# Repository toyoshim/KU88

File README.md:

# KU88
PCB and firmware to convert USB's MD mini controller to PC-8801 keyboard.

# Usage
START button changes the input mode as Normal Mode -> Tenkey Mode -> Normal Mode ...

## Normal Mode
Suitable keymap for RPG games such as The Legend of Heroes, and Hydlide.
Keyname written inside `()` is used while SELECT is pressed.
```
 7(7) 8(8) 9(9)
 4(4)  +   6(6)    F1(W) F2(R) F3(C)
 1(1) 2(2) 3(3)     RET   SPC  Z(ESC)
```
The numbers are 10-Key variants without the START being pressed, and normal one
with the START being pressed.
 
## Tenkey Mode
Suitable keymap for ADV games such as JESUS.
```
      S(V)       
 Y(Z)  +   N(C)     1(7)  2(8)  3(9)
     SPC(X)         0(4)  ,(5)  .(6)
```

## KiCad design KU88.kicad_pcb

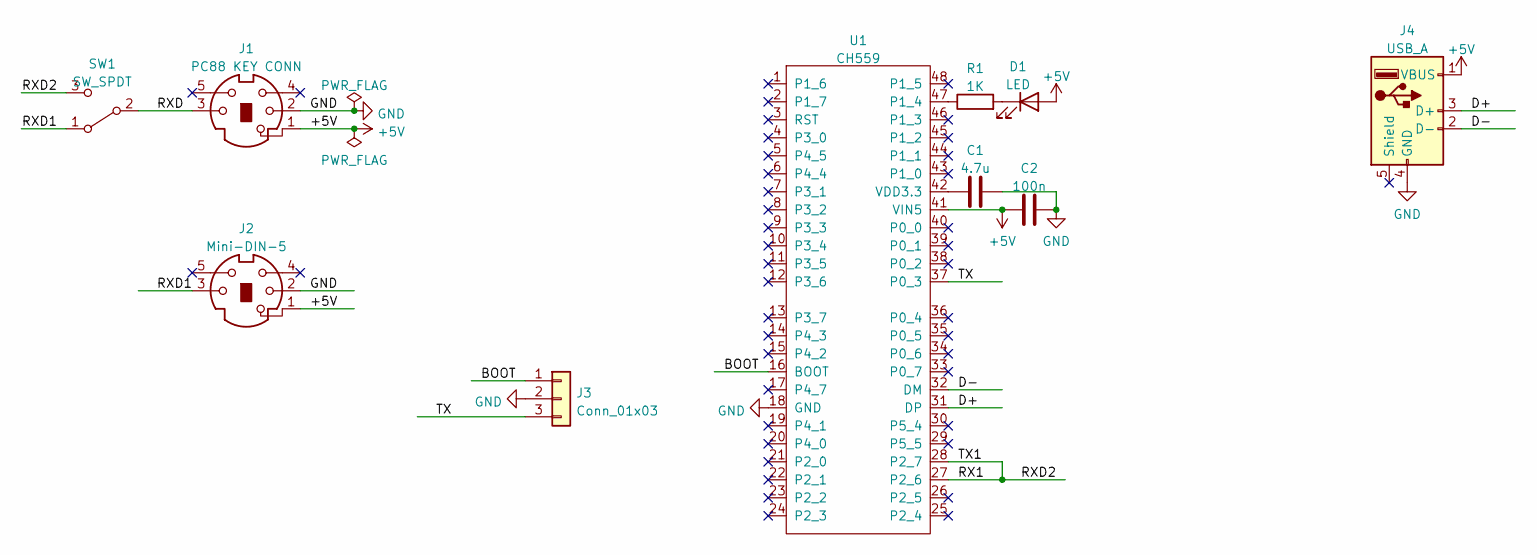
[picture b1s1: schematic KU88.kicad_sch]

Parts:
C1: 4.7u; C_0603_1608Metric_Pad1.08x0.95mm_HandSolder
C2: 100n; C_0603_1608Metric_Pad1.08x0.95mm_HandSolder
D1: LED; D_0603_1608Metric_Pad1.05x0.95mm_HandSolder
J1: PC88 KEY CONN; Mini-DIN 5 Pin Connector
J2: Mini-DIN-5; Mini-DIN 5 Pin Connector
J3: Conn_01x03; PinHeader_1x03_P2.54mm_Vertical
J4: USB_A; USB_A_Female_USB-AF-DIP-154-HW-S
R1: 1K; R_0603_1608Metric_Pad0.98x0.95mm_HandSolder
SW1: SW_SPDT; Switch_Slide_11.6x4mm_EG1218
U1: CH559; LQFP-48_7x7mm_P0.5mm

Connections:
+5V: C2.1, D1.2 (A), J1.1, J2.1, J4.1 (VBUS), U1.41 (VIN5)
/BOOT: J3.1, U1.16 (BOOT)
/D+: J4.3 (D+), U1.31 (DP)
/D-: J4.2 (D-), U1.32 (DM)
/RX1: SW1.3 (C), U1.27 (P2_6), U1.28 (P2_7)
/RXD: J1.3, SW1.2 (B)
/RXD1: J2.3, SW1.1 (A)
/TX: J3.3, U1.37 (P0_3)
GND: C1.2, C2.2, J1.2, J2.2, J3.2, J4.4 (GND), U1.18 (GND)
unnamed: C1.1, U1.42 (VDD3.3)
unnamed: D1.1 (K), R1.2
unnamed: R1.1, U1.47 (P1_4)

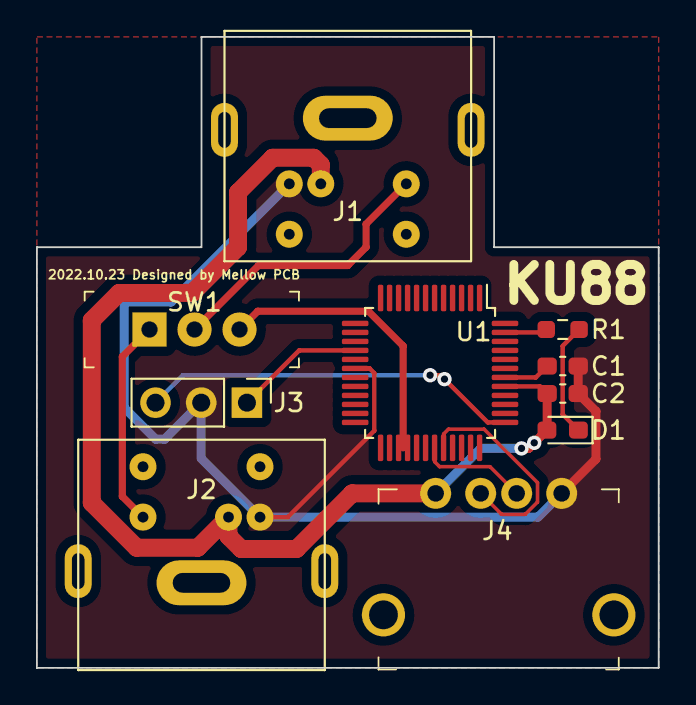
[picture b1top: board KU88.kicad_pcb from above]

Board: 2 copper layers, 34.5 x 35.1 mm, 10 parts (0 on the bottom side), 12 nets.

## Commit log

2022-11-08 firmware initial version
2022-11-16 change the 10key mode to fit playing space mouse
2022-11-17 JESUS; ZXCVCXZC
2023-06-24 update for celia
